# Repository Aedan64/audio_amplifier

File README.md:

# TPA3110D2 Stereo Audio Amplifier

A custom stereo Class-D audio amplifier based on the Texas Instruments
TPA3110D2 amplifier IC. The board is intended to power two 4-ohm automotive
speakers as a desktop audio system.

> **Project status:** Schematic development and component selection.
> This design has not yet been manufactured or electrically tested.

## Design Goals

- Stereo audio output
- Approximately 15 W per channel into 4-ohm speakers
- 3.5 mm stereo audio input
- External DC power input
- LC output filters
- Adjustable or fixed amplifier gain
- Power-limit configuration
- Input and power-supply protection
- Compact PCB suitable for a desktop speaker enclosure

## Main Component

The amplifier is built around the Texas Instruments **TPA3110D2**, a
two-channel Class-D audio power amplifier.

Important features include:

- Two bridge-tied-load output channels
- Differential audio inputs
- Gain-selection pins
- Power-limit control
- Shutdown and mute functions
- Overtemperature, overcurrent, and undervoltage protection

See the [TPA3110D2 datasheet](docs/datasheets/tpa3110d2.pdf) for complete
electrical specifications.

## Target Specifications

| Parameter | Target |
|---|---:|
| Amplifier IC | TPA3110D2 |
| Number of channels | 2 |
| Speaker impedance | 4 ohms |
| Target output power | Approximately 15 W per channel |
| Audio input | 3.5 mm stereo jack |
| Power input | External DC supply |
| Output filtering | LC filter on each BTL output |
| PCB software | KiCad |

The final power-supply voltage and current rating will be documented after
the output-power calculations and component selections are finalized.

## Circuit Sections

The schematic is divided into the following sections:

1. DC power input and input protection
2. Power-supply filtering and decoupling
3. Left and right audio inputs
4. TPA3110D2 amplifier
5. Gain and power-limit configuration
6. LC output filters
7. Left and right speaker connectors

## Output Filters

Each amplifier output uses an LC low-pass filter to reduce switching-frequency
energy before the signal reaches the speaker.

Because the TPA3110D2 uses bridge-tied-load outputs, neither speaker terminal
is connected directly to ground.

Current planned filter components:

- Inductor: 22 uH
- Capacitors: 2.2uF
- Load: 4-ohm speaker

The capacitor values, voltage ratings, current ratings, and filter response
will be verified before PCB layout.

## Power Supply

The board will use an external regulated DC supply connected through a
dedicated power connector.

The following items must be finalized:

- Input voltage
- Required continuous current
- Connector type and polarity
- Fuse or resettable fuse
- Reverse-polarity protection
- Transient-voltage protection

## Opening the Project

1. Install a compatible version of [KiCad](https://www.kicad.org/).
2. Clone or download this repository.
3. Open `amplifier.kicad_pro`.
4. Use KiCad's Schematic Editor to inspect the circuit.
5. Use PCB Editor after footprints have been assigned.

KiCAD version 10.0.5

## Project Status

- [x] Select amplifier IC
- [x] Choose stereo 4-ohm configuration
- [x] Create initial schematic
- [x] Add power-limit voltage divider
- [x] Add LC output filters
- [x] Finalize power-input protection
- [ ] Select exact component part numbers
- [ ] Assign footprints
- [ ] Run KiCad Electrical Rules Checker
- [ ] Create PCB layout
- [ ] Run Design Rules Checker
- [ ] Generate manufacturing files
- [ ] Assemble prototype
- [ ] Test output power, noise, and temperature

## Testing Plan

Before connecting the final speakers, the prototype should be tested for:

- Correct power-supply polarity
- Supply current with no audio input
- DC voltage across each speaker output
- Shutdown and mute behavior
- Output waveform using a resistive dummy load
- Clipping level
- Output power
- Amplifier and inductor temperature
- Noise or oscillation at the speaker outputs

## Known Limitations

This project is under development. Component values, footprints, supply
requirements, and PCB layout may change. Do not treat the current design as a
tested production circuit.

## Documentation

- TPA3110D2 datasheet
- Schematic PDF
- Bill of materials
- PCB images
- Fabrication files
- Prototype test results

These documents will be added as the project progresses.

## Author

Aedan Lewis

Electrical Engineering student project.

## License

A license has not yet been selected.

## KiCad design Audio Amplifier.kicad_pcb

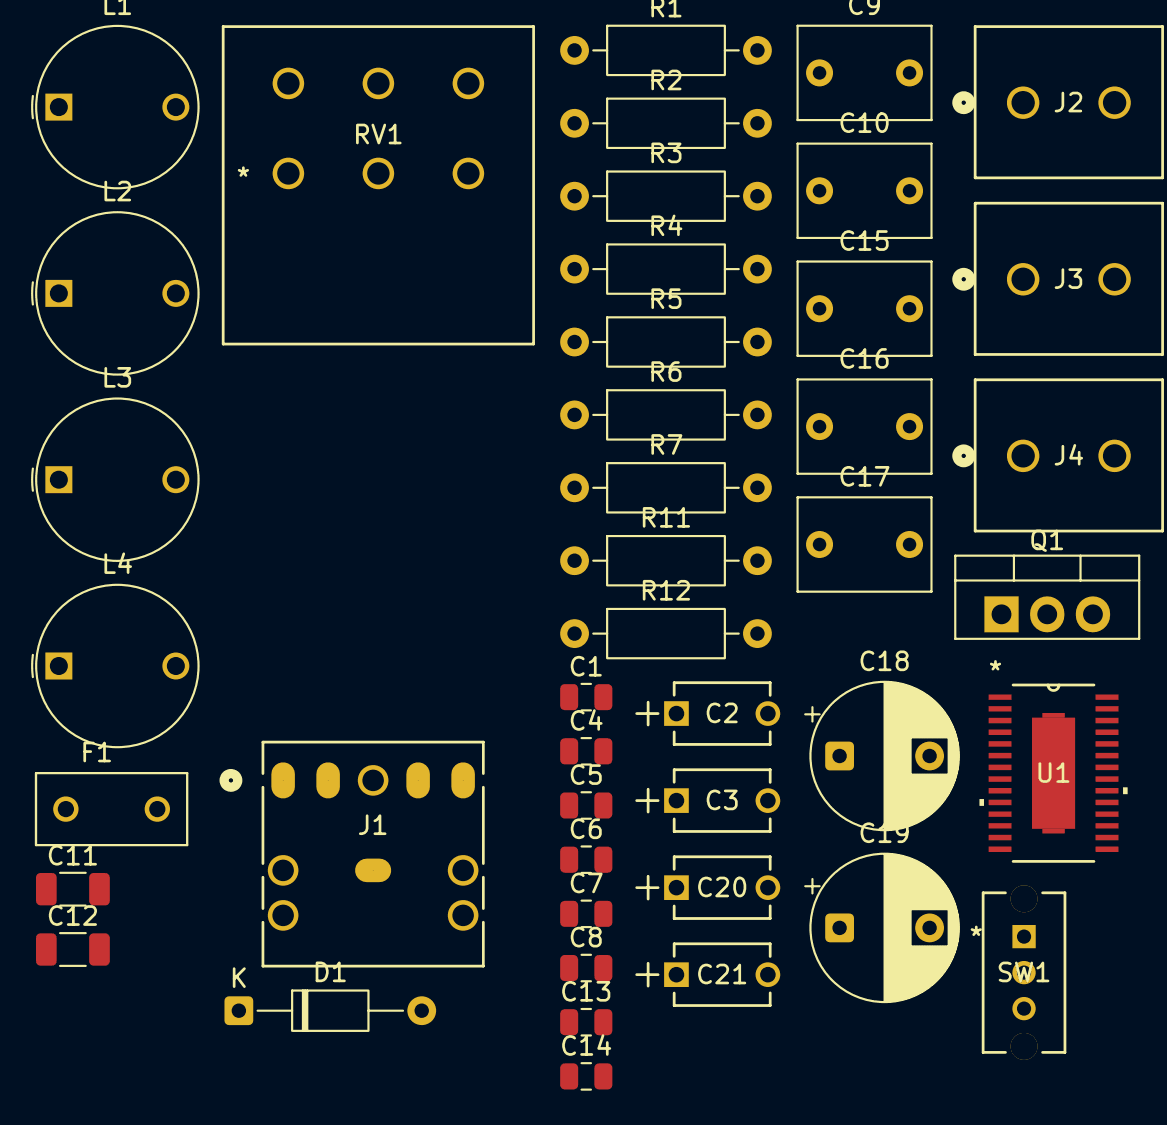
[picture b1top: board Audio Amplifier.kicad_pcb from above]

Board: 2 copper layers, 44 parts (0 on the bottom side), 31 nets, no tracks yet.

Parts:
C1, C4, C13, C14: 0.22uF; C_0805_2012Metric
C2, C3, C20, C21: 2.2uF; CAP_C322C_MR_X7R_KEM
C5, C7: 0.1uF; C_0805_2012Metric
C6, C8: 1000pF; C_0805_2012Metric
C9, C10, C15, C16, C17: 1uF; C_Rect_L7.2mm_W5.0mm_P5.00mm
C11, C12: 1uF; C_1206_3216Metric
C18, C19: 220uF; CP_Radial_D8.0mm_P5.00mm
D1: D_Zener; D_DO-35_SOD27_P10.16mm_Horizontal
F1: 4A time delay; FUSRR508W60L840T400H810B
J1: AudioJack3; SJ1-3523N_CUD
J2: +12V 5A regulated power supply; CONN_1729128_PXC
J3: RIGHT_4ohm-SPEAKER; CONN_1729128_PXC
J4: LEFT_4ohm_SPEAKER; CONN_1729128_PXC
L1, L2, L3, L4: 15uH; L_Wurth_WE-FAMI-8010_LeadDiameter0.5mm
Q1: Q_PMOS_GDS; TO-220-3_Vertical
R1, R2: 100k; R_Axial_DIN0207_L6.3mm_D2.5mm_P10.16mm_Horizontal
R3, R4, R6: 1k; R_Axial_DIN0207_L6.3mm_D2.5mm_P10.16mm_Horizontal
R5: 10; R_Axial_DIN0207_L6.3mm_D2.5mm_P10.16mm_Horizontal
R7, R12: 10k; R_Axial_DIN0207_L6.3mm_D2.5mm_P10.16mm_Horizontal
R11: 13k; R_Axial_DIN0207_L6.3mm_D2.5mm_P10.16mm_Horizontal
RV1: A10k; PDB-182-K_20K_BRN
SW1: SW_SPDT; SPDT_OS102011_CNK
U1: TPA3110D2PWP; PWP28_6P17X2P4

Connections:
12V: C5.1, C6.1, C7.1, C8.1, C18.1, C19.1, D1.1 (K), Q1.3 (S), R1.2, R5.1, U1.15 (PVCCR), U1.16 (PVCCR), U1.27 (PVCCL), U1.28 (PVCCL)
/AVCC: C11.1, R2.1, R5.2, U1.7 (AVCC)
/GVDD: C12.2, R11.2, U1.9 (GVDD)
/InL: C9.2, U1.3 (LINP)
/InR: C16.2, U1.12 (RINP)
/PLIM: C17.1, R11.1, R12.2, U1.10 (PLIMIT)
GND: C2.2, C3.1, C5.2, C6.2, C7.2, C8.2, C10.1, C11.2, C12.1, C15.1, C17.2, C18.2, C19.2, C20.2, C21.1, J2.1, R7.1, R12.1, RV1.1, RV1.4, SW1.1 (A), U1.6 (GAIN1), U1.8 (AGND), U1.14 (PBTL), U1.19 (PGND), U1.24 (PGND), U1.29 (EPAD)
unnamed: C9.1, RV1.5
unnamed: C16.1, RV1.2
unnamed: D1.2 (A), Q1.1 (G), R7.2
unnamed: F1.1, J2.2
unnamed: C20.1, L2.2
unnamed: C21.2, L3.2
unnamed: C2.1, L1.2
unnamed: C3.2, L4.2
unnamed: F1.2, Q1.2 (D)
unnamed: R3.2, RV1.6
unnamed: R4.2, RV1.3
unnamed: R6.2, SW1.2 (B)
unnamed: R1.1, R6.1, U1.1 (*SD), U1.2 (*FAULT)
unnamed: C4.1, U1.22 (BSNL)
unnamed: C13.1, U1.21 (BSNR)
unnamed: C1.1, U1.26 (BSPL)
unnamed: C14.1, U1.17 (BSPR)
unnamed: R2.2, U1.5 (GAIN0)
unnamed: C15.2, U1.4 (LINN)
unnamed: C4.2, L4.1, U1.23 (OUTNL)
unnamed: C13.2, L2.1, U1.20 (OUTNR)
unnamed: C1.2, L1.1, U1.25 (OUTPL)
unnamed: C14.2, L3.1, U1.18 (OUTPR)
unnamed: C10.2, U1.11 (RINN)
